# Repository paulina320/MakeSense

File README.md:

# MakeSense

MakeSense is the hardware and software toolkit for the EuroHaptics 2026
workshop on data-driven haptic texture reproduction.

## Repository layout

- [`host/`](host/) — PyQt6 application for recording, modelling,
  characterization, compensation, and rendering.
- [`device/firmware/stm32_haptic_device/`](device/firmware/stm32_haptic_device/)
  — active STM32 firmware.
- [`device/pcb_files/`](device/pcb_files/) — KiCad sources and manufacturing
  outputs for the MakeSense hardware.
- [`Documents/`](Documents/) — workshop flyer, kit guide, schedule, and banner.

See the [host README](host/README.md) for installation and application usage.

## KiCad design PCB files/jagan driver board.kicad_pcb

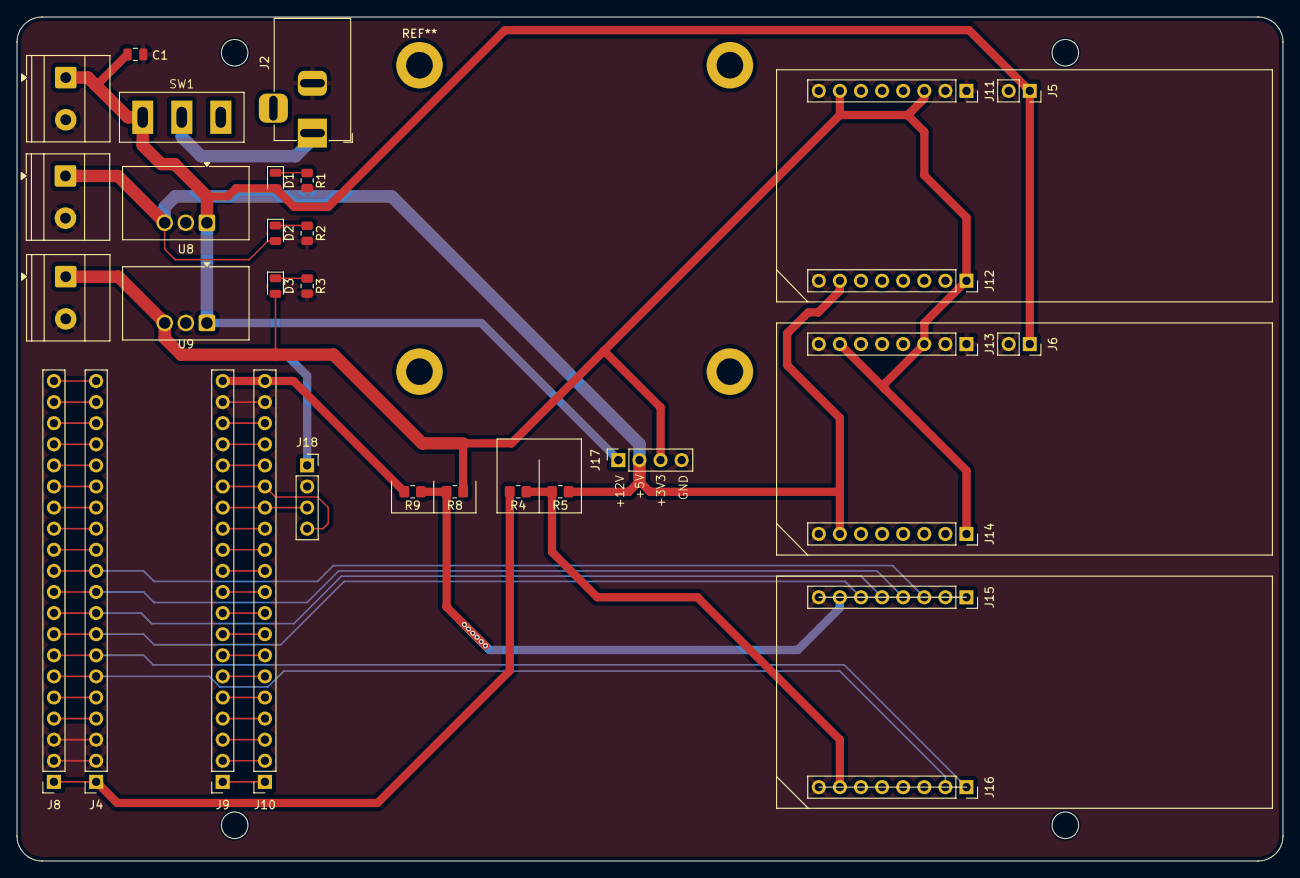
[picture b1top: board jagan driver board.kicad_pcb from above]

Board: 2 copper layers, 152.4 x 101.6 mm, 36 parts (0 on the bottom side), 47 nets.

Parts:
C1: 10uF; C_0805_2012Metric
D1, D2, D3: LED; LED_0805_2012Metric
H1, H2, H3, H4: MountingHole; MountingHole_3.2mm_M3
J1, J3, J7: Screw_Terminal_01x02; TerminalBlock_Phoenix_MKDS-1,5-2-5.08_1x02_P5.08mm_Horizont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
J2: Barrel_Jack; BarrelJack_Horizontal
J4: MCU 2; PinSocket_1x20_P2.54mm_Vertical
J5, J6: Conn_01x02_Pin; PinSocket_1x02_P2.54mm_Vertical
J8, J9, J10: Conn_01x20_Pin; PinSocket_1x20_P2.54mm_Vertical
J11, J12, J13, J14, J15, J16: Conn_01x08_Pin; PinSocket_1x08_P2.54mm_Vertical
J17, J18: Conn_01x04_Pin; PinSocket_1x04_P2.54mm_Vertical
R1: 1K; R_0805_2012Metric
R2: 150E; R_0805_2012Metric
R3: 100E; R_0805_2012Metric
R4, R5, R8, R9: 0E; R_0805_2012Metric_Pad1.20x1.40mm_HandSolder
SW1: SW_SPDT; K3-1391A-51
U8: TSR3-2450N; Converter_DCDC_TRACO_TSR2-24xxN_TSR2-24xxxN_THT
U9: TSR3-2433N; Converter_DCDC_TRACO_TSR2-24xxN_TSR2-24xxxN_THT

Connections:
+3.3V_MCU: J9.20, J10.20, R9.2
+3V3: D3.2 (A), J3.1, J11.3, J11.7, J12.1, J13.3, J13.7, J14.1, J17.3, J18.1, R8.1, U9.3 (Vout)
+5V: D2.2 (A), J1.1, J12.7, J14.7, J17.2, R5.1, U8.3 (Vout)
+5V_MCU: J4.1, J8.1, R4.2
+12V: C1.1, D1.2 (A), J5.1, J6.1, J7.1, J17.1, SW1.1 (A), U8.1 (Vin), U9.1 (Vin)
/Main Schematic/PIXI_CS: J4.11, J8.11, J15.3
/Main Schematic/PIXI_CVNT: J4.7, J8.7, J16.1
/Main Schematic/PIXI_INT: J4.6, J8.6, J16.2
/Main Schematic/PIXI_MISO: J4.9, J8.9, J15.5
/Main Schematic/PIXI_MOSI: J4.8, J8.8, J15.6
/Main Schematic/PIXI_SCLK: J4.10, J8.10, J15.4
/Main Schematic/SCL 1: J9.14, J10.14, J18.3
/Main Schematic/SDA 1: J9.15, J10.15, J18.4
GND: C1.2, J1.2, J2.2, J3.2, J4.2, J4.3, J5.2, J6.2, J7.2, J8.2, J8.3, J9.19, J10.19, J11.1, J11.2, J11.8, J12.8, J13.1, J13.2, J13.8, J14.8, J15.8, J16.8, J17.4, J18.2, R1.2, R2.2, R3.2, U8.2 (GND), U9.2 (GND)
unnamed: D1.1 (K), R1.1
unnamed: D2.1 (K), R2.1
unnamed: D3.1 (K), R3.1
unnamed: J4.4, J8.4
unnamed: J4.5, J8.5
unnamed: J4.12, J8.12
unnamed: J4.13, J8.13
unnamed: J4.14, J8.14
unnamed: J4.15, J8.15
unnamed: J4.16, J8.16
unnamed: J4.17, J8.17
unnamed: J4.18, J8.18
unnamed: J4.19, J8.19
unnamed: J4.20, J8.20
unnamed: J9.1, J10.1
unnamed: J9.2, J10.2
unnamed: J9.3, J10.3
unnamed: J9.4, J10.4
unnamed: J9.5, J10.5
unnamed: J9.6, J10.6
unnamed: J9.7, J10.7
unnamed: J9.8, J10.8
unnamed: J9.9, J10.9
unnamed: J9.10, J10.10
unnamed: J9.11, J10.11
unnamed: J9.12, J10.12
unnamed: J9.13, J10.13
unnamed: J9.16, J10.16
unnamed: J9.17, J10.17
unnamed: J9.18, J10.18
unnamed: J15.7, R8.2, R9.1
unnamed: J16.7, R4.1, R5.2
unnamed: J2.1, SW1.2 (B)

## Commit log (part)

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2026-03-03 add textures
2026-03-03 Update install instructions
2026-03-03 Remove unused UI element from CompensationWidget
2026-04-10 Revise title for haptic texture workshop
    Updated workshop title and description in README.
2026-06-01 Expand README with hardware components information
    Added detailed hardware components section to README.
2026-06-26 Included updated manual
2026-06-26 Rename MakeSense_Kit_EuroHaptics_2026.pdf to Documents/MakeSense_Kit_EuroHaptics_2026.pdf
2026-06-26 Added documents
2026-06-26 Rename Flyer Eurohaptics_2026.pdf to Documents/Flyer Eurohaptics_2026.pdf
2026-06-26 added schedule
2026-06-30 Added PCB files.
2026-06-30 Upload readme banner
2026-06-30 Add banner image to README
